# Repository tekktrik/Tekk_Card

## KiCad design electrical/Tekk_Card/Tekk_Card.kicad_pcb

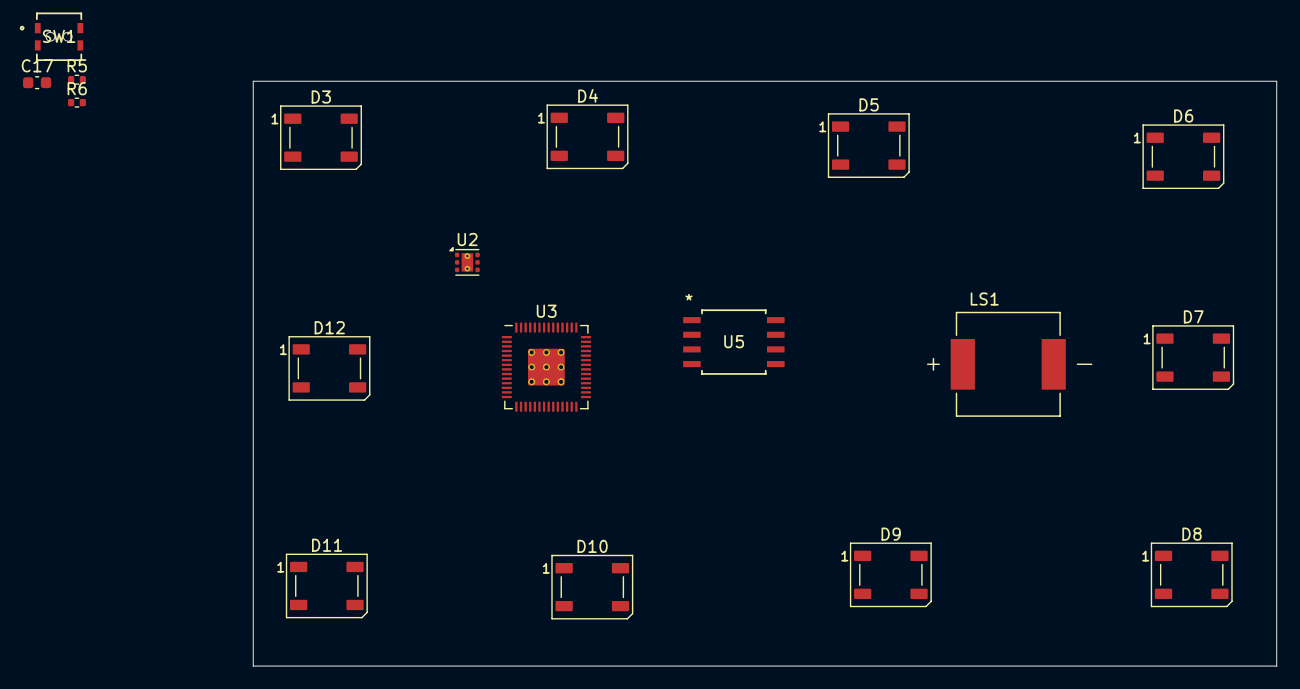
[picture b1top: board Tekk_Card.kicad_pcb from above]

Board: 2 copper layers, 88.9 x 50.8 mm, 18 parts (0 on the bottom side), 20 nets, no tracks yet.

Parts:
C17: 100nF; C_0603_1608Metric
D3, D4, D5, D6, D7, D8, D9, D10, D11, D12: WS2812B; LED_WS2812B_PLCC4_5.0x5.0mm_P3.2mm
LS1: SMTB-0940-T-3V-R; XDCR_SMTB-0940-T-3V-R
R5: 10k; R_0402_1005Metric
R6: 1k; R_0402_1005Metric
SW1: SW_Push; R-667_MIT
U2: TLV76733DRVx; WSON-6-1EP_2x2mm_P0.65mm_EP1x1.6mm_ThermalVias
U3: RP2040; RP2040-QFN-56
U5: W25Q64JVSSIQ; SOIC-8_5P28X5P28_WIN

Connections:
+1V1: U3.23 (DVDD), U3.45 (VREG_VOUT), U3.50 (DVDD)
+3V3: C17.1, D3.1 (VDD), D4.1 (VDD), D5.1 (VDD), D6.1 (VDD), D7.1 (VDD), D8.1 (VDD), D9.1 (VDD), D10.1 (VDD), D11.1 (VDD), D12.1 (VDD), R5.1, U2.1 (OUT), U2.2 (SNS), U3.1 (IOVDD), U3.10 (IOVDD), U3.22 (IOVDD), U3.42 (IOVDD), U3.43 (ADC_AVDD), U3.44 (VREG_IN), U3.48 (USB_VDD), U3.49 (IOVDD), U5.8 (VCC)
/Flash & Boot/QSPI_SCLK: U3.52 (QSPI_SCLK), U5.6 (CLK)
/Flash & Boot/QSPI_SD0: U3.53 (QSPI_SD0), U5.5 (DI(IO0))
/Flash & Boot/QSPI_SD1: U3.55 (QSPI_SD1), U5.2 (DO(IO1))
/Flash & Boot/QSPI_SD2: U3.54 (QSPI_SD2), U5.3 (/WP(IO2))
/Flash & Boot/QSPI_SD3: U3.51 (QSPI_SD3), U5.7 (/HOLD_OR_/RESET(IO3))
/Flash & Boot/QSPI_SS: R5.2, R6.2, U3.56 (QSPI_SS), U5.1 (/CS)
/Lighting/NEOPIXEL: D3.4 (DIN), U3.8 (GPIO6)
GND: C17.2, D3.3 (VSS), D4.3 (VSS), D5.3 (VSS), D6.3 (VSS), D7.3 (VSS), D8.3 (VSS), D9.3 (VSS), D10.3 (VSS), D11.3 (VSS), D12.3 (VSS), LS1.N, SW1.1, U2.3 (GND), U2.5 (GND), U2.7 (PAD), U5.4 (GND)
unnamed: D3.2 (DOUT), D4.4 (DIN)
unnamed: D4.2 (DOUT), D5.4 (DIN)
unnamed: D5.2 (DOUT), D6.4 (DIN)
unnamed: D6.2 (DOUT), D7.4 (DIN)
unnamed: D7.2 (DOUT), D8.4 (DIN)
unnamed: D8.2 (DOUT), D9.4 (DIN)
unnamed: D9.2 (DOUT), D10.4 (DIN)
unnamed: D11.2 (DOUT), D11.4 (DIN), D12.4 (DIN)
unnamed: R6.1, SW1.2
VBUS: U2.4 (EN), U2.6 (IN)

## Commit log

2025-10-03 Continue initial prototype
